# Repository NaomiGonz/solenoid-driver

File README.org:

** Single Channel Solenoid Driver

#+attr_org: :width 500px
[[file:./images/driver-v0.png]]

A prototype single channel solenoid driver was developed for testing.

It is contained in the ~driver-v0~ folder.

We will have 3 manifolds with 8 of these in a row that need to be driven with 12V and signalled with a TTL line. All the manifolds will act in unison.

 - https://www.theleeco.com/product/lhd-series-2-way-control-solenoid-valve/
 - 3 boards, 8 channels each
 - 8 TTL inputs + GND
 - 8 12V outputs
 - 12V input on barrel jack
   - Plug:
     - https://www.digikey.com/en/products/detail/globtek-inc/CRP11856F00/16515770
     - Cable Assembly 2.1mm ID, 5.5mm OD Jack, Right Angle to Wire Leads Round 6.0' (1.83m)
   - Jack:
     - https://www.digikey.com/en/products/detail/cui-devices/PJ-063AH/2161208
     - PJ-063AH Power Barrel Connector Jack 2.10mm ID (0.083"), 5.50mm OD (0.217") Through Hole, Right Angle
 - LHDB1242115H
 - Spike+hold voltage: 12, 7.2
 - LOHM RATE** (Cv): 1500 Lohms (0.013)
 - Power Consumption At Hold Voltage (mW): 310
 - Response time: 10 ms Max

|----+-----------+-----+----------------------+--------------------+---------------------------|
|  # | Reference | Qty | Value                | PartNum            | Mfg                       |
|----+-----------+-----+----------------------+--------------------+---------------------------|
|  1 | C1        |   1 | 47uF                 | T491X476K035AT     | Kemet                     |
|  2 | C3        |   1 | 10uF                 | CL32A106KLULNNE    | Samsung Electro-Mechanics |
|  3 | C4        |   1 | 0.18 uF              | 08053C184KAT2A     | KYOCERA AVX               |
|  4 | C5        |   1 | 470pF                | C0805C471K5RAC7800 | Kemet                     |
|  5 | D1        |   1 | LED                  | 150080RS75000      | Wurth                     |
|  6 | D2        |   1 | PMEG10010ELRX        | PMEG10010ELRX      | Nexperia                  |
|  7 | F1        |   1 | 0ZCF0125FF2C         | 0ZCF0125FF2C       | Bel Fuse                  |
|  8 | J1, J2    |   2 | Screw_Terminal_01x02 | 282837-2           | TE                        |
|  9 | J3        |   1 | Barrel_Jack          | PJ-063AH           | CUI                       |
| 10 | R1        |   1 | 49R9                 | RC0805FR-0749R9L   | Yageo                     |
| 11 | R2        |   1 | 191k                 | RC0805FR-07191KL   | Yageo                     |
| 12 | R3        |   1 | 162k                 | RC0805FR-07162KL   | Yageo                     |
| 13 | R4, R5    |   2 | 4k7                  | RC0805JR-074K7L    | Yageo                     |
| 14 | U1        |   1 | DRV104PWP            | DRV104PWP          | TI                        |
|----+-----------+-----+----------------------+--------------------+---------------------------|

** Octal Channel Driver

** Dual Channel Complementary Driver

We will also have a pair of these valves that need to be driven by a single TTL
line in opposition (if one is in state A the other should be in state B).
 - LHDA1231415H
 - https://www.theleeco.com/product/lhd-series-3-way-control-solenoid-valve/
 - One TTL input  + GND
 - Two 12V complementary outputs

The solenoids should be driven with a high-side switch using a peak and hold circuit.

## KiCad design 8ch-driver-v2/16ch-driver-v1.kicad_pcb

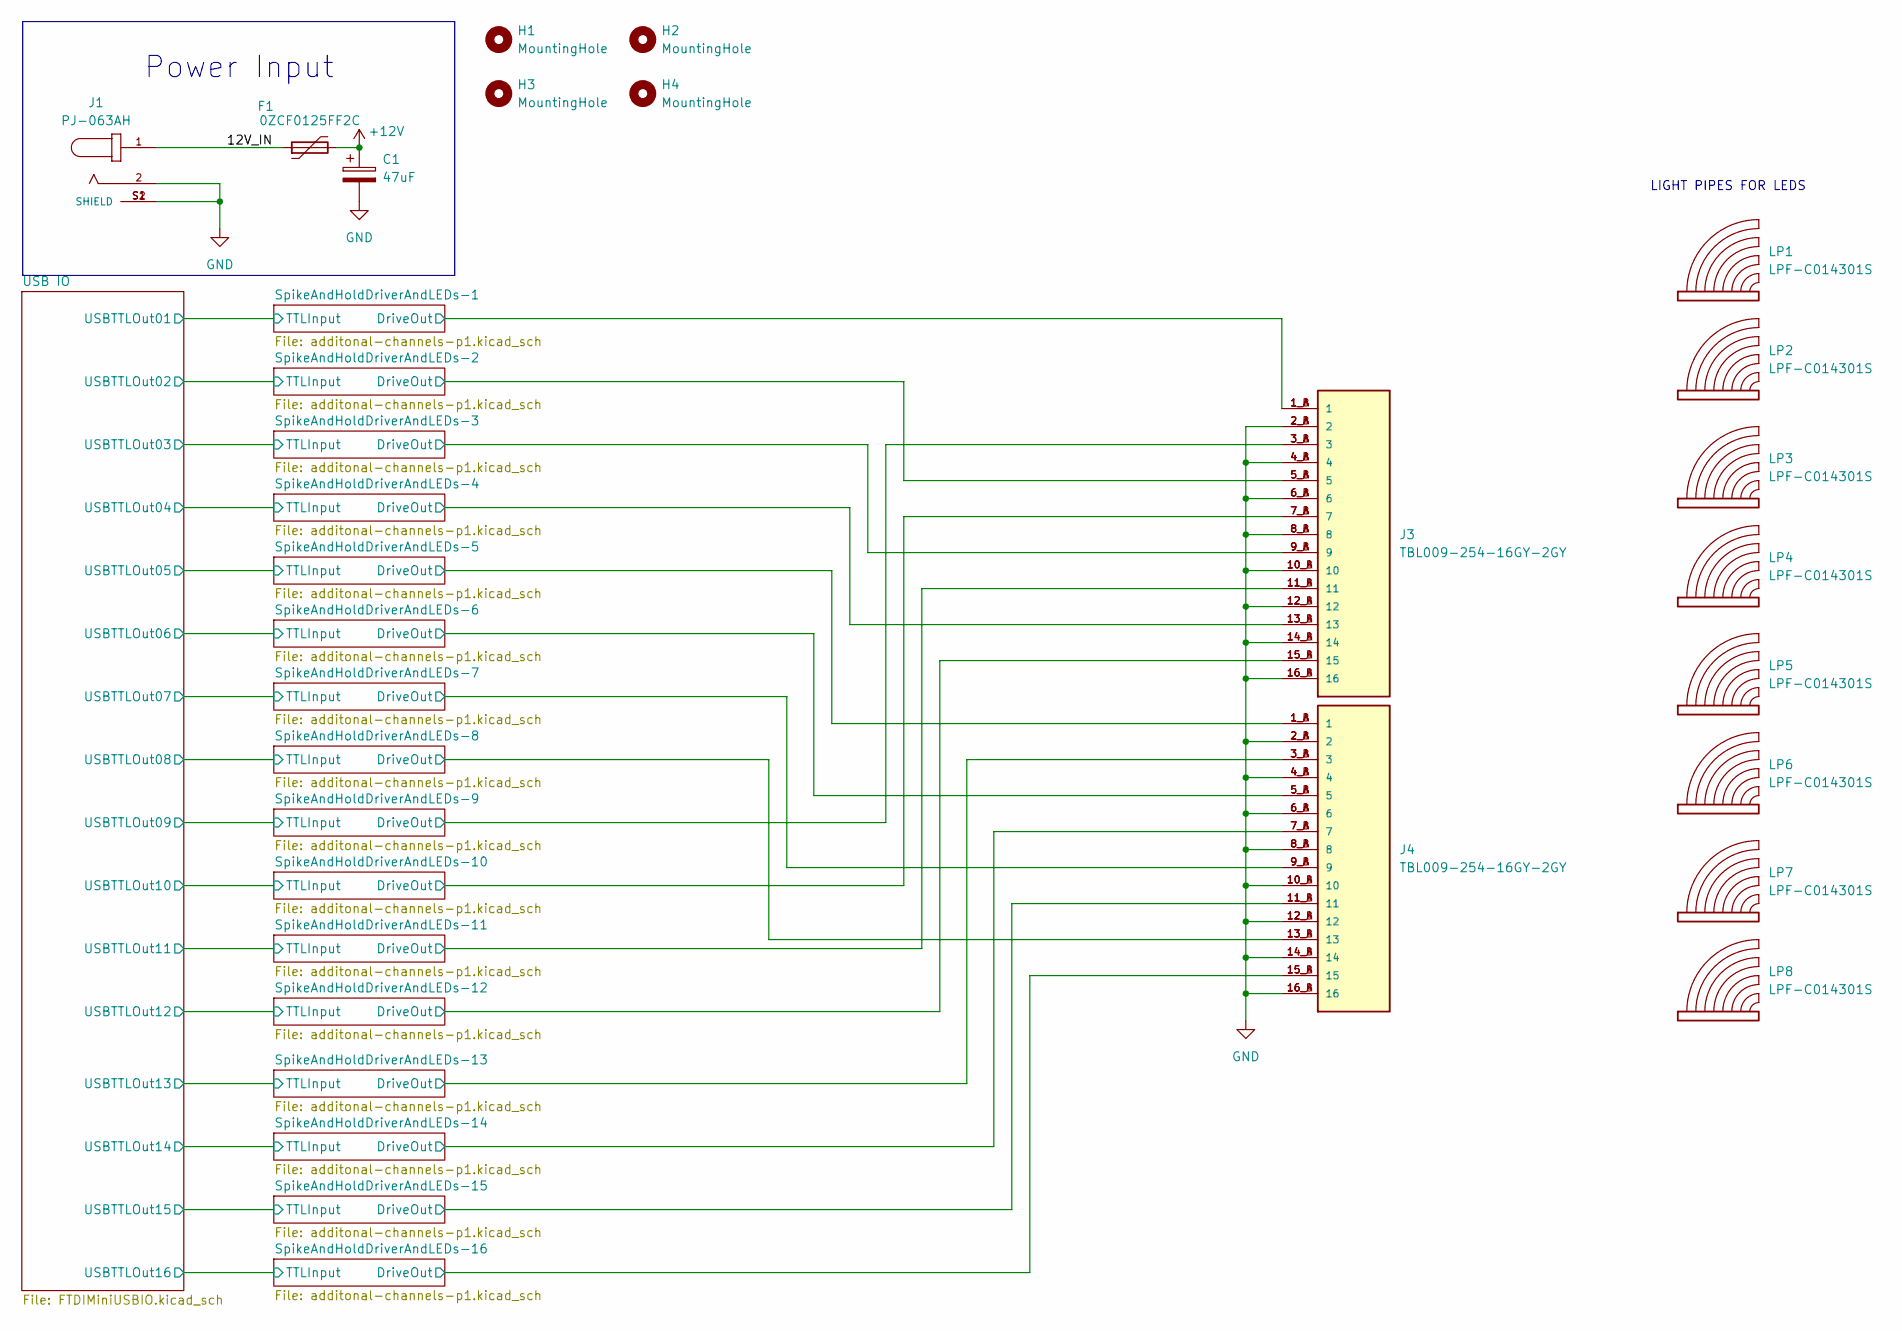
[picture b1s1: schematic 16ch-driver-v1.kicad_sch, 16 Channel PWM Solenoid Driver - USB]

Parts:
C1: 47uF; CP_EIA-7343-43_Kemet-X_Pad2.25x2.55mm_HandSolder; PartNum T491X476K035AT
F1: 0ZCF0125FF2C; Fuse_2920_7451Metric; PartNum 0ZCF0125FF2C
H1, H2, H3, H4: MountingHole; MountingHole_3.2mm_M3
J1: PJ-063AH; CUI_PJ-063AH; PARTREV 1.02
J3, J4: TBL009-254-16GY-2GY; CUI_TBL009-254-16GY-2GY
LP1, LP2, LP3, LP4, LP5, LP6, LP7, LP8: LPF-C014301S; Lightpipe_LPF-C014301S

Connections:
+12V: C1.1, F1.2; also elsewhere on the board
/12V_IN: F1.1, J1.1
/SpikeAndHoldDriverAndLEDs-1/DriveOut: J3.1_A (1), J3.1_B (1); also elsewhere on the board
/SpikeAndHoldDriverAndLEDs-2/DriveOut: J3.5_A (5), J3.5_B (5); also elsewhere on the board
/SpikeAndHoldDriverAndLEDs-3/DriveOut: J3.9_A (9), J3.9_B (9); also elsewhere on the board
/SpikeAndHoldDriverAndLEDs-4/DriveOut: J3.13_A (13), J3.13_B (13); also elsewhere on the board
/SpikeAndHoldDriverAndLEDs-5/DriveOut: J4.1_A (1), J4.1_B (1); also elsewhere on the board
/SpikeAndHoldDriverAndLEDs-6/DriveOut: J4.5_A (5), J4.5_B (5); also elsewhere on the board
/SpikeAndHoldDriverAndLEDs-7/DriveOut: J4.9_A (9), J4.9_B (9); also elsewhere on the board
/SpikeAndHoldDriverAndLEDs-8/DriveOut: J4.13_A (13), J4.13_B (13); also elsewhere on the board
/SpikeAndHoldDriverAndLEDs-9/DriveOut: J3.3_A (3), J3.3_B (3); also elsewhere on the board
/SpikeAndHoldDriverAndLEDs-10/DriveOut: J3.7_A (7), J3.7_B (7); also elsewhere on the board
/SpikeAndHoldDriverAndLEDs-11/DriveOut: J3.11_A (11), J3.11_B (11); also elsewhere on the board
/SpikeAndHoldDriverAndLEDs-12/DriveOut: J3.15_A (15), J3.15_B (15); also elsewhere on the board
/SpikeAndHoldDriverAndLEDs-13/DriveOut: J4.3_A (3), J4.3_B (3); also elsewhere on the board
/SpikeAndHoldDriverAndLEDs-14/DriveOut: J4.7_A (7), J4.7_B (7); also elsewhere on the board
/SpikeAndHoldDriverAndLEDs-15/DriveOut: J4.11_A (11), J4.11_B (11); also elsewhere on the board
/SpikeAndHoldDriverAndLEDs-16/DriveOut: J4.15_A (15), J4.15_B (15); also elsewhere on the board
GND: C1.2, J1.2, J1.S1 (SHIELD), J1.S2 (SHIELD), J3.2_A (2), J3.2_B (2), J3.4_A (4), J3.4_B (4), J3.6_A (6), J3.6_B (6), J3.8_A (8), J3.8_B (8), J3.10_A (10), J3.10_B (10), J3.12_A (12), J3.12_B (12), J3.14_A (14), J3.14_B (14), J3.16_A (16), J3.16_B (16), J4.2_A (2), J4.2_B (2), J4.4_A (4), J4.4_B (4), J4.6_A (6), J4.6_B (6), J4.8_A (8), J4.8_B (8), J4.10_A (10), J4.10_B (10), J4.12_A (12), J4.12_B (12), J4.14_A (14), J4.14_B (14), J4.16_A (16), J4.16_B (16); also elsewhere on the board

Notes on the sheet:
Power Input
LIGHT PIPES FOR LEDS

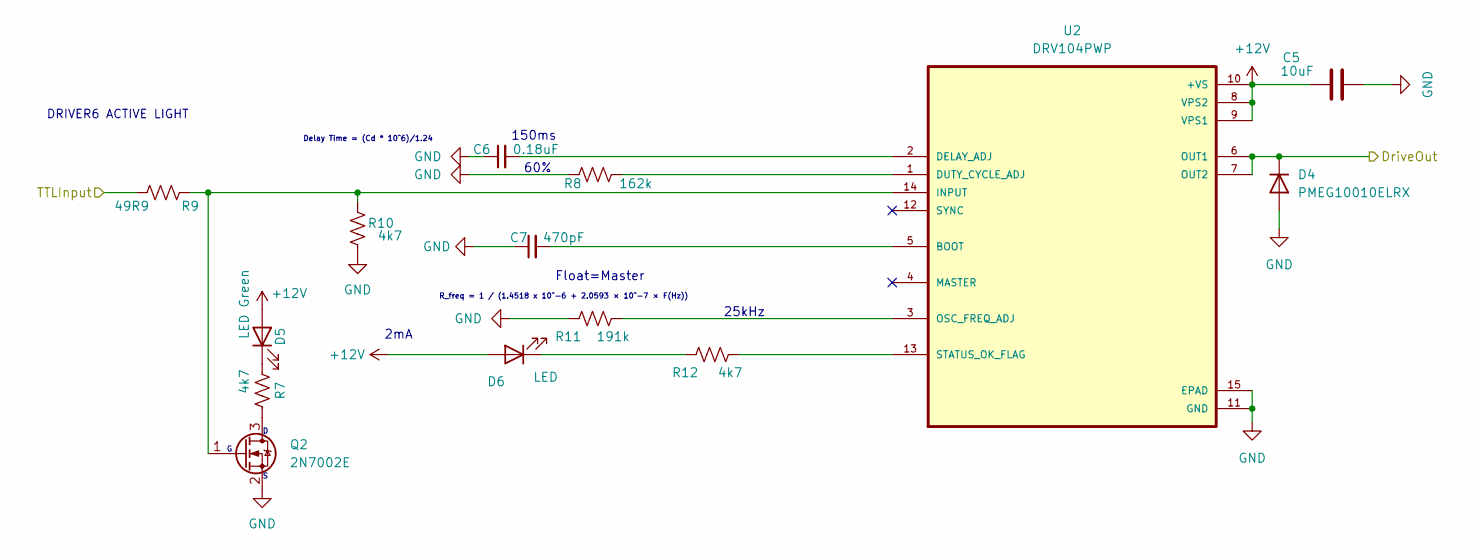
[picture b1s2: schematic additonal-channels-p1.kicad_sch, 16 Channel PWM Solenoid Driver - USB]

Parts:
C5: 10uF; C_1210_3225Metric; PartNum CL32A106KLULNNE
C6: 0.18uF; C_1206_3216Metric; PartNum 08053C184KAT2A
C7: 470pF; C_1206_3216Metric; PartNum C0805C471K5RAC7800
D4: PMEG10010ELRX; Nexperia_CFP3_SOD-123W; PartNum PMEG10010ELRX
D5: LED Green; LED_0805_2012Metric; PartNum 150080RS75000
D6: LED; LED_0805_2012Metric; PartNum 150080RS75000
Q2: 2N7002E; SOT-23
R7: 4k7; R_1206_3216Metric; PartNum RC0805FR-07162KL
R8: 162k; R_1206_3216Metric; PartNum RC0805FR-07162KL
R9: 49R9; R_1206_3216Metric; PartNum RC0805FR-0749R9L
R10, R12: 4k7; R_1206_3216Metric; PartNum RC0805JR-074K7L
R11: 191k; R_1206_3216Metric; PartNum RC0805FR-07191KL
U2: DRV104PWP; IC_TPS27S100BPWPR; PartNum DRV104PWP

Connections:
+12V: C5.1, D5.2 (A), D6.2 (A), U2.8 (VPS2), U2.9 (VPS1), U2.10 (+VS); also elsewhere on the board
/SpikeAndHoldDriverAndLEDs-2/DriveOut: D4.1 (K), U2.6 (OUT1), U2.7 (OUT2); also elsewhere on the board
/SpikeAndHoldDriverAndLEDs-2/TTLInput: R9.1; also elsewhere on the board
GND: C5.2, C6.1, C7.1, D4.2 (A), Q2.2 (S), R8.1, R10.1, R11.1, U2.11 (GND), U2.15 (EPAD); also elsewhere on the board
unnamed: D5.1 (K), R7.1
unnamed: D6.1 (K), R12.1
unnamed: Q2.3 (D), R7.2
unnamed: Q2.1 (G), R9.2, R10.2, U2.14 (INPUT)
unnamed: C7.2, U2.5 (BOOT)
unnamed: C6.2, U2.2 (DELAY_ADJ)
unnamed: R8.2, U2.1 (DUTY_CYCLE_ADJ)
unnamed: R11.2, U2.3 (OSC_FREQ_ADJ)
unnamed: R12.2, U2.13 (STATUS_OK_FLAG)

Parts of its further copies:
C2, C8, C11, C14, C17, C20, C23, C26, C29, C32, C35, C38, C41, C44, C47: 10uF; C_1210_3225Metric; PartNum CL32A106KLULNNE
C3, C9, C12, C15, C18, C21, C24, C27, C30, C33, C36, C39, C42, C45, C48: 0.18uF; C_1206_3216Metric; PartNum 08053C184KAT2A
C4, C10, C13, C16, C19, C22, C25, C28, C31, C34, C37, C40, C43, C46, C49: 470pF; C_1206_3216Metric; PartNum C0805C471K5RAC7800
D1, D7, D10, D13, D16, D19, D22, D25, D28, D31, D34, D37, D40, D43, D46: PMEG10010ELRX; Nexperia_CFP3_SOD-123W; PartNum PMEG10010ELRX
D2, D8, D11, D14, D17, D20, D23, D26, D29, D32, D35, D38, D41, D44, D47: LED Green; LED_0805_2012Metric; PartNum 150080RS75000
D3, D9, D12, D15, D18, D21, D24, D27, D30, D33, D36, D39, D42, D45, D48: LED; LED_0805_2012Metric; PartNum 150080RS75000
Q1, Q3, Q4, Q5, Q6, Q7, Q8, Q9, Q10, Q11, Q12, Q13, Q14, Q15, Q16: 2N7002E; SOT-23
R1, R13, R19, R25, R31, R37, R43, R49, R55, R61, R67, R73, R79, R85, R91: 4k7; R_1206_3216Metric; PartNum RC0805FR-07162KL
R2, R14, R20, R26, R32, R38, R44, R50, R56, R62, R68, R74, R80, R86, R92: 162k; R_1206_3216Metric; PartNum RC0805FR-07162KL
R3, R15, R21, R27, R33, R39, R45, R51, R57, R63, R69, R75, R81, R87, R93: 49R9; R_1206_3216Metric; PartNum RC0805FR-0749R9L
R4, R6, R16, R18, R22, R24, R28, R30, R34, R36, R40, R42, R46, R48, R52, R54, R58, R60, R64, R66, R70, R72, R76, R78, R82, R84, R88, R90, R94, R96: 4k7; R_1206_3216Metric; PartNum RC0805JR-074K7L
R5, R17, R23, R29, R35, R41, R47, R53, R59, R65, R71, R77, R83, R89, R95: 191k; R_1206_3216Metric; PartNum RC0805FR-07191KL
U1, U3, U4, U5, U6, U7, U8, U9, U10, U11, U12, U13, U14, U15, U16: DRV104PWP; IC_TPS27S100BPWPR; PartNum DRV104PWP

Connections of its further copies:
+12V: C2.1, C8.1, C11.1, C14.1, C17.1, C20.1, C23.1, C26.1, C29.1, C32.1, C35.1, C38.1, C41.1, C44.1, C47.1, D2.2 (A), D3.2 (A), D8.2 (A), D9.2 (A), D11.2 (A), D12.2 (A), D14.2 (A), D15.2 (A), D17.2 (A), D18.2 (A), D20.2 (A), D21.2 (A), D23.2 (A), D24.2 (A), D26.2 (A), D27.2 (A), D29.2 (A), D30.2 (A), D32.2 (A), D33.2 (A), D35.2 (A), D36.2 (A), D38.2 (A), D39.2 (A), D41.2 (A), D42.2 (A), D44.2 (A), D45.2 (A), D47.2 (A), D48.2 (A), U1.8 (VPS2), U1.9 (VPS1), U1.10 (+VS), U3.8 (VPS2), U3.9 (VPS1), U3.10 (+VS), U4.8 (VPS2), U4.9 (VPS1), U4.10 (+VS), U5.8 (VPS2), U5.9 (VPS1), U5.10 (+VS), U6.8 (VPS2), U6.9 (VPS1), U6.10 (+VS), U7.8 (VPS2), U7.9 (VPS1), U7.10 (+VS), U8.8 (VPS2), U8.9 (VPS1), U8.10 (+VS), U9.8 (VPS2), U9.9 (VPS1), U9.10 (+VS), U10.8 (VPS2), U10.9 (VPS1), U10.10 (+VS), U11.8 (VPS2), U11.9 (VPS1), U11.10 (+VS), U12.8 (VPS2), U12.9 (VPS1), U12.10 (+VS), U13.8 (VPS2), U13.9 (VPS1), U13.10 (+VS), U14.8 (VPS2), U14.9 (VPS1), U14.10 (+VS), U15.8 (VPS2), U15.9 (VPS1), U15.10 (+VS), U16.8 (VPS2), U16.9 (VPS1), U16.10 (+VS); also elsewhere on the board
/SpikeAndHoldDriverAndLEDs-1/DriveOut: D1.1 (K), U1.6 (OUT1), U1.7 (OUT2); also elsewhere on the board
/SpikeAndHoldDriverAndLEDs-1/TTLInput: R3.1; also elsewhere on the board
/SpikeAndHoldDriverAndLEDs-3/DriveOut: D7.1 (K), U3.6 (OUT1), U3.7 (OUT2); also elsewhere on the board
/SpikeAndHoldDriverAndLEDs-3/TTLInput: R15.1; also elsewhere on the board
/SpikeAndHoldDriverAndLEDs-4/DriveOut: D10.1 (K), U4.6 (OUT1), U4.7 (OUT2); also elsewhere on the board
/SpikeAndHoldDriverAndLEDs-4/TTLInput: R21.1; also elsewhere on the board
/SpikeAndHoldDriverAndLEDs-5/DriveOut: D13.1 (K), U5.6 (OUT1), U5.7 (OUT2); also elsewhere on the board
/SpikeAndHoldDriverAndLEDs-5/TTLInput: R27.1; also elsewhere on the board
/SpikeAndHoldDriverAndLEDs-6/DriveOut: D16.1 (K), U6.6 (OUT1), U6.7 (OUT2); also elsewhere on the board
/SpikeAndHoldDriverAndLEDs-6/TTLInput: R33.1; also elsewhere on the board
/SpikeAndHoldDriverAndLEDs-7/DriveOut: D19.1 (K), U7.6 (OUT1), U7.7 (OUT2); also elsewhere on the board
/SpikeAndHoldDriverAndLEDs-7/TTLInput: R39.1; also elsewhere on the board
/SpikeAndHoldDriverAndLEDs-8/DriveOut: D22.1 (K), U8.6 (OUT1), U8.7 (OUT2); also elsewhere on the board
/SpikeAndHoldDriverAndLEDs-8/TTLInput: R45.1; also elsewhere on the board
/SpikeAndHoldDriverAndLEDs-9/DriveOut: D25.1 (K), U9.6 (OUT1), U9.7 (OUT2); also elsewhere on the board
/SpikeAndHoldDriverAndLEDs-9/TTLInput: R51.1; also elsewhere on the board
/SpikeAndHoldDriverAndLEDs-10/DriveOut: D28.1 (K), U10.6 (OUT1), U10.7 (OUT2); also elsewhere on the board
/SpikeAndHoldDriverAndLEDs-10/TTLInput: R57.1; also elsewhere on the board
/SpikeAndHoldDriverAndLEDs-11/DriveOut: D31.1 (K), U11.6 (OUT1), U11.7 (OUT2); also elsewhere on the board
/SpikeAndHoldDriverAndLEDs-11/TTLInput: R63.1; also elsewhere on the board
/SpikeAndHoldDriverAndLEDs-12/DriveOut: D34.1 (K), U12.6 (OUT1), U12.7 (OUT2); also elsewhere on the board
/SpikeAndHoldDriverAndLEDs-12/TTLInput: R69.1; also elsewhere on the board
/SpikeAndHoldDriverAndLEDs-13/DriveOut: D37.1 (K), U13.6 (OUT1), U13.7 (OUT2); also elsewhere on the board
/SpikeAndHoldDriverAndLEDs-13/TTLInput: R75.1; also elsewhere on the board
/SpikeAndHoldDriverAndLEDs-14/DriveOut: D40.1 (K), U14.6 (OUT1), U14.7 (OUT2); also elsewhere on the board
/SpikeAndHoldDriverAndLEDs-14/TTLInput: R81.1; also elsewhere on the board
/SpikeAndHoldDriverAndLEDs-15/DriveOut: D43.1 (K), U15.6 (OUT1), U15.7 (OUT2); also elsewhere on the board
/SpikeAndHoldDriverAndLEDs-15/TTLInput: R87.1; also elsewhere on the board
/SpikeAndHoldDriverAndLEDs-16/DriveOut: D46.1 (K), U16.6 (OUT1), U16.7 (OUT2); also elsewhere on the board
/SpikeAndHoldDriverAndLEDs-16/TTLInput: R93.1; also elsewhere on the board
GND: C2.2, C3.1, C4.1, C8.2, C9.1, C10.1, C11.2, C12.1, C13.1, C14.2, C15.1, C16.1, C17.2, C18.1, C19.1, C20.2, C21.1, C22.1, C23.2, C24.1, C25.1, C26.2, C27.1, C28.1, C29.2, C30.1, C31.1, C32.2, C33.1, C34.1, C35.2, C36.1, C37.1, C38.2, C39.1, C40.1, C41.2, C42.1, C43.1, C44.2, C45.1, C46.1, C47.2, C48.1, C49.1, D1.2 (A), D7.2 (A), D10.2 (A), D13.2 (A), D16.2 (A), D19.2 (A), D22.2 (A), D25.2 (A), D28.2 (A), D31.2 (A), D34.2 (A), D37.2 (A), D40.2 (A), D43.2 (A), D46.2 (A), Q1.2 (S), Q3.2 (S), Q4.2 (S), Q5.2 (S), Q6.2 (S), Q7.2 (S), Q8.2 (S), Q9.2 (S), Q10.2 (S), Q11.2 (S), Q12.2 (S), Q13.2 (S), Q14.2 (S), Q15.2 (S), Q16.2 (S), R2.1, R4.1, R5.1, R14.1, R16.1, R17.1, R20.1, R22.1, R23.1, R26.1, R28.1, R29.1, R32.1, R34.1, R35.1, R38.1, R40.1, R41.1, R44.1, R46.1, R47.1, R50.1, R52.1, R53.1, R56.1, R58.1, R59.1, R62.1, R64.1, R65.1, R68.1, R70.1, R71.1, R74.1, R76.1, R77.1, R80.1, R82.1, R83.1, R86.1, R88.1, R89.1, R92.1, R94.1, R95.1, U1.11 (GND), U1.15 (EPAD), U3.11 (GND), U3.15 (EPAD), U4.11 (GND), U4.15 (EPAD), U5.11 (GND), U5.15 (EPAD), U6.11 (GND), U6.15 (EPAD), U7.11 (GND), U7.15 (EPAD), U8.11 (GND), U8.15 (EPAD), U9.11 (GND), U9.15 (EPAD), U10.11 (GND), U10.15 (EPAD), U11.11 (GND), U11.15 (EPAD), U12.11 (GND), U12.15 (EPAD), U13.11 (GND), U13.15 (EPAD), U14.11 (GND), U14.15 (EPAD), U15.11 (GND), U15.15 (EPAD), U16.11 (GND), U16.15 (EPAD); also elsewhere on the board
unnamed: D2.1 (K), R1.1
unnamed: D3.1 (K), R6.1
unnamed: D8.1 (K), R13.1
unnamed: D9.1 (K), R18.1
unnamed: D11.1 (K), R19.1
unnamed: D12.1 (K), R24.1
unnamed: D14.1 (K), R25.1
unnamed: D15.1 (K), R30.1
unnamed: D17.1 (K), R31.1
unnamed: D18.1 (K), R36.1
unnamed: D20.1 (K), R37.1
unnamed: D21.1 (K), R42.1
unnamed: D23.1 (K), R43.1
unnamed: D24.1 (K), R48.1
unnamed: D26.1 (K), R49.1
unnamed: D27.1 (K), R54.1
unnamed: D29.1 (K), R55.1
unnamed: D30.1 (K), R60.1
unnamed: D32.1 (K), R61.1
unnamed: D33.1 (K), R66.1
unnamed: D35.1 (K), R67.1
unnamed: D36.1 (K), R72.1
unnamed: D38.1 (K), R73.1
unnamed: D39.1 (K), R78.1
unnamed: D41.1 (K), R79.1
unnamed: D42.1 (K), R84.1
unnamed: D44.1 (K), R85.1
unnamed: D45.1 (K), R90.1
unnamed: D47.1 (K), R91.1
unnamed: D48.1 (K), R96.1
unnamed: Q1.3 (D), R1.2
unnamed: Q1.1 (G), R3.2, R4.2, U1.14 (INPUT)
unnamed: Q3.3 (D), R13.2
unnamed: Q3.1 (G), R15.2, R16.2, U3.14 (INPUT)
unnamed: Q4.3 (D), R19.2
unnamed: Q4.1 (G), R21.2, R22.2, U4.14 (INPUT)
unnamed: Q5.3 (D), R25.2
unnamed: Q5.1 (G), R27.2, R28.2, U5.14 (INPUT)
unnamed: Q6.3 (D), R31.2
unnamed: Q6.1 (G), R33.2, R34.2, U6.14 (INPUT)
unnamed: Q7.3 (D), R37.2
unnamed: Q7.1 (G), R39.2, R40.2, U7.14 (INPUT)
unnamed: Q8.3 (D), R43.2
unnamed: Q8.1 (G), R45.2, R46.2, U8.14 (INPUT)
unnamed: Q9.3 (D), R49.2
unnamed: Q9.1 (G), R51.2, R52.2, U9.14 (INPUT)
unnamed: Q10.3 (D), R55.2
unnamed: Q10.1 (G), R57.2, R58.2, U10.14 (INPUT)
unnamed: Q11.3 (D), R61.2
unnamed: Q11.1 (G), R63.2, R64.2, U11.14 (INPUT)
unnamed: Q12.3 (D), R67.2
unnamed: Q12.1 (G), R69.2, R70.2, U12.14 (INPUT)
unnamed: Q13.3 (D), R73.2
unnamed: Q13.1 (G), R75.2, R76.2, U13.14 (INPUT)
unnamed: Q14.3 (D), R79.2
unnamed: Q14.1 (G), R81.2, R82.2, U14.14 (INPUT)
unnamed: Q15.3 (D), R85.2
unnamed: Q15.1 (G), R87.2, R88.2, U15.14 (INPUT)
unnamed: Q16.3 (D), R91.2
unnamed: Q16.1 (G), R93.2, R94.2, U16.14 (INPUT)
unnamed: C4.2, U1.5 (BOOT)
unnamed: C3.2, U1.2 (DELAY_ADJ)
unnamed: R2.2, U1.1 (DUTY_CYCLE_ADJ)
unnamed: R5.2, U1.3 (OSC_FREQ_ADJ)
unnamed: R6.2, U1.13 (STATUS_OK_FLAG)
unnamed: C10.2, U3.5 (BOOT)
unnamed: C9.2, U3.2 (DELAY_ADJ)
unnamed: R14.2, U3.1 (DUTY_CYCLE_ADJ)
unnamed: R17.2, U3.3 (OSC_FREQ_ADJ)
unnamed: R18.2, U3.13 (STATUS_OK_FLAG)
unnamed: C13.2, U4.5 (BOOT)
unnamed: C12.2, U4.2 (DELAY_ADJ)
unnamed: R20.2, U4.1 (DUTY_CYCLE_ADJ)
unnamed: R23.2, U4.3 (OSC_FREQ_ADJ)
unnamed: R24.2, U4.13 (STATUS_OK_FLAG)
unnamed: C16.2, U5.5 (BOOT)
unnamed: C15.2, U5.2 (DELAY_ADJ)
unnamed: R26.2, U5.1 (DUTY_CYCLE_ADJ)
unnamed: R29.2, U5.3 (OSC_FREQ_ADJ)
unnamed: R30.2, U5.13 (STATUS_OK_FLAG)
unnamed: C19.2, U6.5 (BOOT)
unnamed: C18.2, U6.2 (DELAY_ADJ)
unnamed: R32.2, U6.1 (DUTY_CYCLE_ADJ)
unnamed: R35.2, U6.3 (OSC_FREQ_ADJ)
unnamed: R36.2, U6.13 (STATUS_OK_FLAG)
unnamed: C22.2, U7.5 (BOOT)
unnamed: C21.2, U7.2 (DELAY_ADJ)
unnamed: R38.2, U7.1 (DUTY_CYCLE_ADJ)
unnamed: R41.2, U7.3 (OSC_FREQ_ADJ)
unnamed: R42.2, U7.13 (STATUS_OK_FLAG)
unnamed: C25.2, U8.5 (BOOT)
unnamed: C24.2, U8.2 (DELAY_ADJ)
unnamed: R44.2, U8.1 (DUTY_CYCLE_ADJ)
unnamed: R47.2, U8.3 (OSC_FREQ_ADJ)
unnamed: R48.2, U8.13 (STATUS_OK_FLAG)
unnamed: C28.2, U9.5 (BOOT)
unnamed: C27.2, U9.2 (DELAY_ADJ)
unnamed: R50.2, U9.1 (DUTY_CYCLE_ADJ)
unnamed: R53.2, U9.3 (OSC_FREQ_ADJ)
unnamed: R54.2, U9.13 (STATUS_OK_FLAG)
unnamed: C31.2, U10.5 (BOOT)
unnamed: C30.2, U10.2 (DELAY_ADJ)
unnamed: R56.2, U10.1 (DUTY_CYCLE_ADJ)
unnamed: R59.2, U10.3 (OSC_FREQ_ADJ)
unnamed: R60.2, U10.13 (STATUS_OK_FLAG)
unnamed: C34.2, U11.5 (BOOT)
unnamed: C33.2, U11.2 (DELAY_ADJ)
unnamed: R62.2, U11.1 (DUTY_CYCLE_ADJ)
unnamed: R65.2, U11.3 (OSC_FREQ_ADJ)
unnamed: R66.2, U11.13 (STATUS_OK_FLAG)
unnamed: C37.2, U12.5 (BOOT)
unnamed: C36.2, U12.2 (DELAY_ADJ)
unnamed: R68.2, U12.1 (DUTY_CYCLE_ADJ)
unnamed: R71.2, U12.3 (OSC_FREQ_ADJ)
unnamed: R72.2, U12.13 (STATUS_OK_FLAG)
unnamed: C40.2, U13.5 (BOOT)
unnamed: C39.2, U13.2 (DELAY_ADJ)
unnamed: R74.2, U13.1 (DUTY_CYCLE_ADJ)
unnamed: R77.2, U13.3 (OSC_FREQ_ADJ)
unnamed: R78.2, U13.13 (STATUS_OK_FLAG)
unnamed: C43.2, U14.5 (BOOT)
unnamed: C42.2, U14.2 (DELAY_ADJ)
unnamed: R80.2, U14.1 (DUTY_CYCLE_ADJ)
unnamed: R83.2, U14.3 (OSC_FREQ_ADJ)
unnamed: R84.2, U14.13 (STATUS_OK_FLAG)
unnamed: C46.2, U15.5 (BOOT)
unnamed: C45.2, U15.2 (DELAY_ADJ)
unnamed: R86.2, U15.1 (DUTY_CYCLE_ADJ)
unnamed: R89.2, U15.3 (OSC_FREQ_ADJ)
unnamed: R90.2, U15.13 (STATUS_OK_FLAG)
unnamed: C49.2, U16.5 (BOOT)
unnamed: C48.2, U16.2 (DELAY_ADJ)
unnamed: R92.2, U16.1 (DUTY_CYCLE_ADJ)
unnamed: R95.2, U16.3 (OSC_FREQ_ADJ)
unnamed: R96.2, U16.13 (STATUS_OK_FLAG)

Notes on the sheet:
2mA
60%
150ms
Float=Master
25kHz
Delay Time = (Cd * 10^6)/1.24
DRIVER6 ACTIVE LIGHT
R_freq = 1 / (1.4518 x 10^−6 + 2.0593 × 10^−7 × F(Hz))

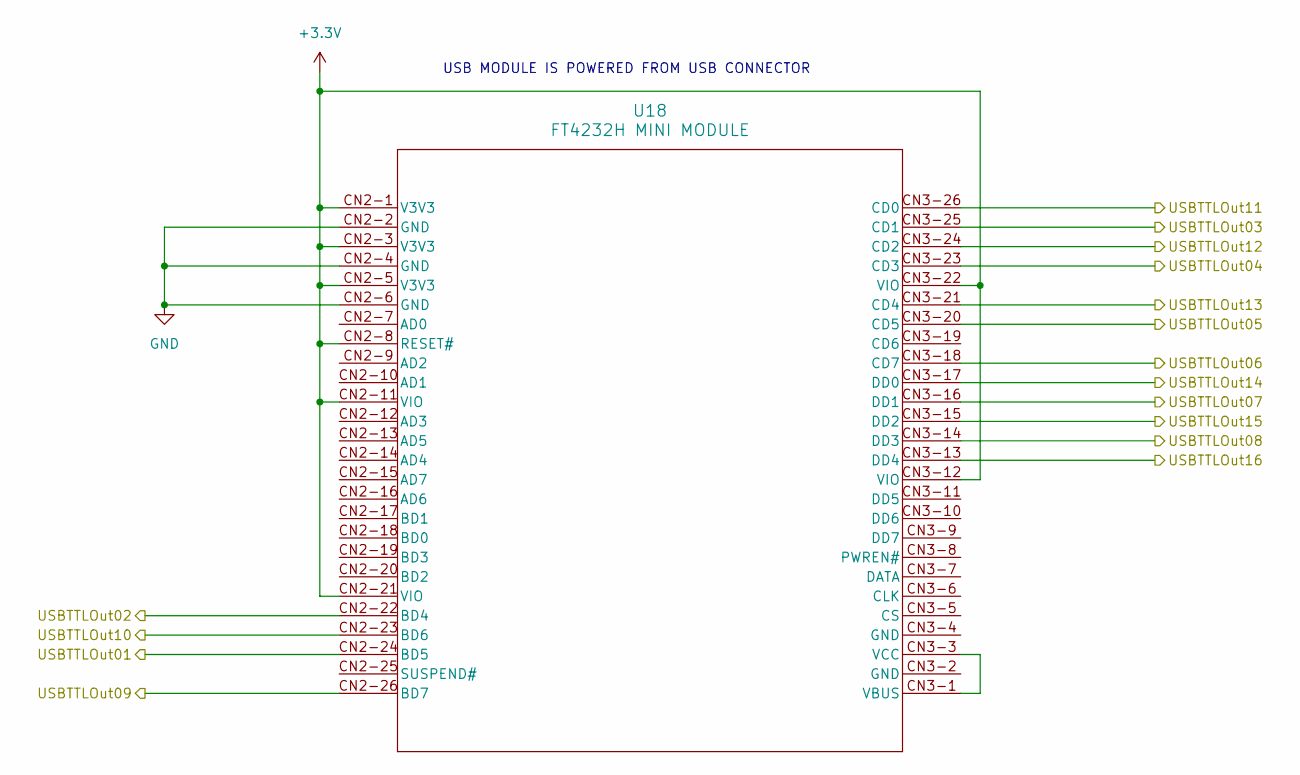
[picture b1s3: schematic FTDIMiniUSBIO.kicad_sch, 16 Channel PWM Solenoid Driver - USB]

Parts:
U18: FT4232H MINI MODULE; FT4232H_MINI_MODULE

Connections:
+3.3V: U18.CN2-1 (V3V3), U18.CN2-3 (V3V3), U18.CN2-5 (V3V3), U18.CN2-8 (RESET#), U18.CN2-11 (VIO), U18.CN2-21 (VIO), U18.CN3-12 (VIO), U18.CN3-22 (VIO)
/SpikeAndHoldDriverAndLEDs-1/TTLInput: U18.CN2-24 (BD5); also elsewhere on the board
/SpikeAndHoldDriverAndLEDs-2/TTLInput: U18.CN2-22 (BD4); also elsewhere on the board
/SpikeAndHoldDriverAndLEDs-3/TTLInput: U18.CN3-25 (CD1); also elsewhere on the board
/SpikeAndHoldDriverAndLEDs-4/TTLInput: U18.CN3-23 (CD3); also elsewhere on the board
/SpikeAndHoldDriverAndLEDs-5/TTLInput: U18.CN3-20 (CD5); also elsewhere on the board
/SpikeAndHoldDriverAndLEDs-6/TTLInput: U18.CN3-18 (CD7); also elsewhere on the board
/SpikeAndHoldDriverAndLEDs-7/TTLInput: U18.CN3-16 (DD1); also elsewhere on the board
/SpikeAndHoldDriverAndLEDs-8/TTLInput: U18.CN3-14 (DD3); also elsewhere on the board
/SpikeAndHoldDriverAndLEDs-9/TTLInput: U18.CN2-26 (BD7); also elsewhere on the board
/SpikeAndHoldDriverAndLEDs-10/TTLInput: U18.CN2-23 (BD6); also elsewhere on the board
/SpikeAndHoldDriverAndLEDs-11/TTLInput: U18.CN3-26 (CD0); also elsewhere on the board
/SpikeAndHoldDriverAndLEDs-12/TTLInput: U18.CN3-24 (CD2); also elsewhere on the board
/SpikeAndHoldDriverAndLEDs-13/TTLInput: U18.CN3-21 (CD4); also elsewhere on the board
/SpikeAndHoldDriverAndLEDs-14/TTLInput: U18.CN3-17 (DD0); also elsewhere on the board
/SpikeAndHoldDriverAndLEDs-15/TTLInput: U18.CN3-15 (DD2); also elsewhere on the board
/SpikeAndHoldDriverAndLEDs-16/TTLInput: U18.CN3-13 (DD4); also elsewhere on the board
GND: U18.CN2-2 (GND), U18.CN2-4 (GND), U18.CN2-6 (GND); also elsewhere on the board
unnamed: U18.CN3-1 (VBUS), U18.CN3-3 (VCC)

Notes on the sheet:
USB MODULE IS POWERED FROM USB CONNECTOR

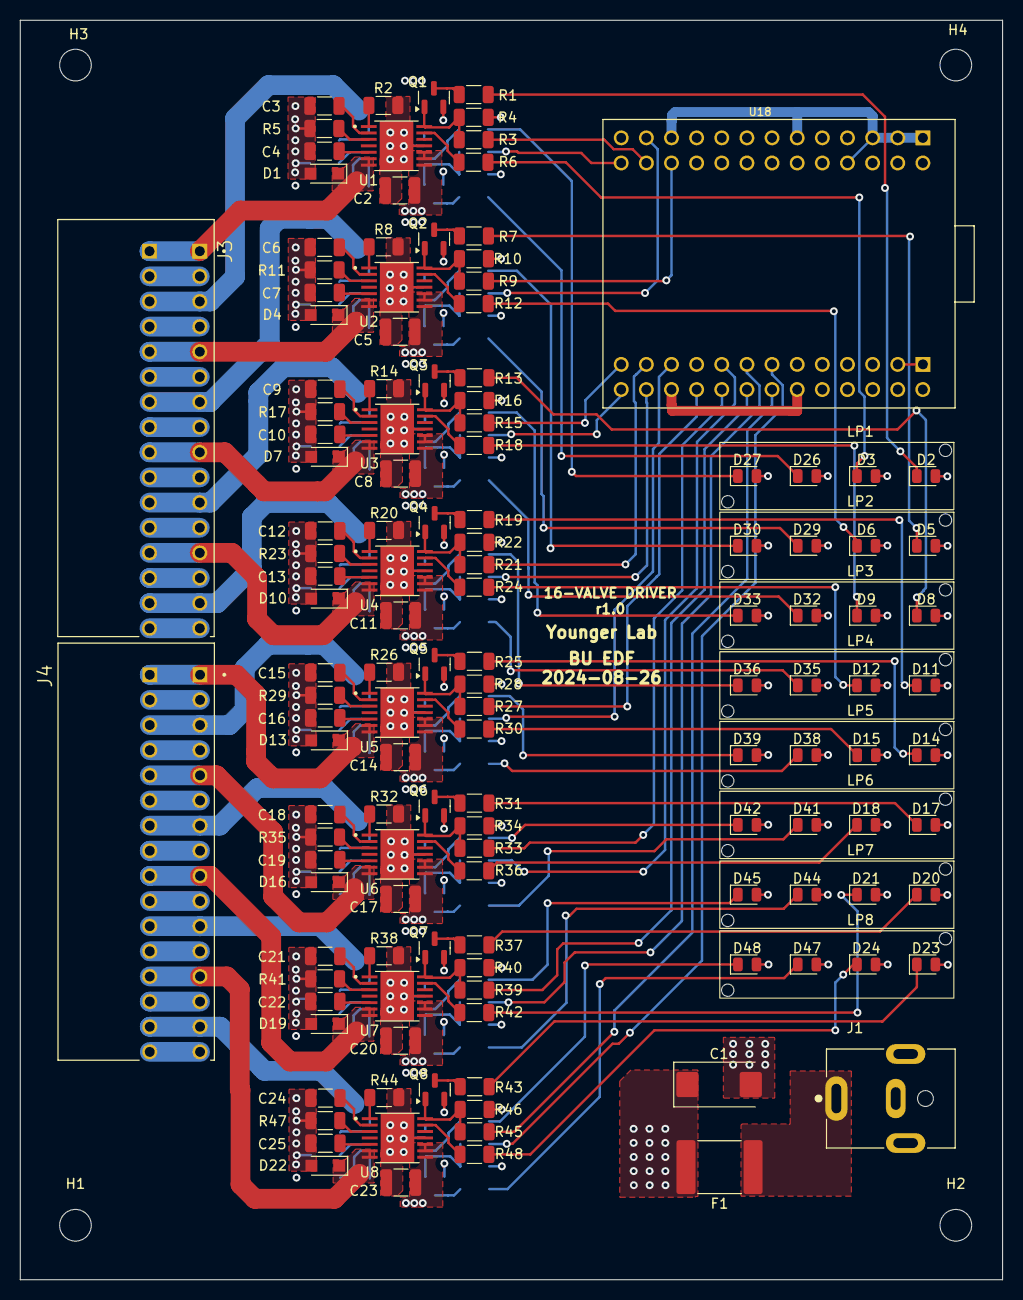
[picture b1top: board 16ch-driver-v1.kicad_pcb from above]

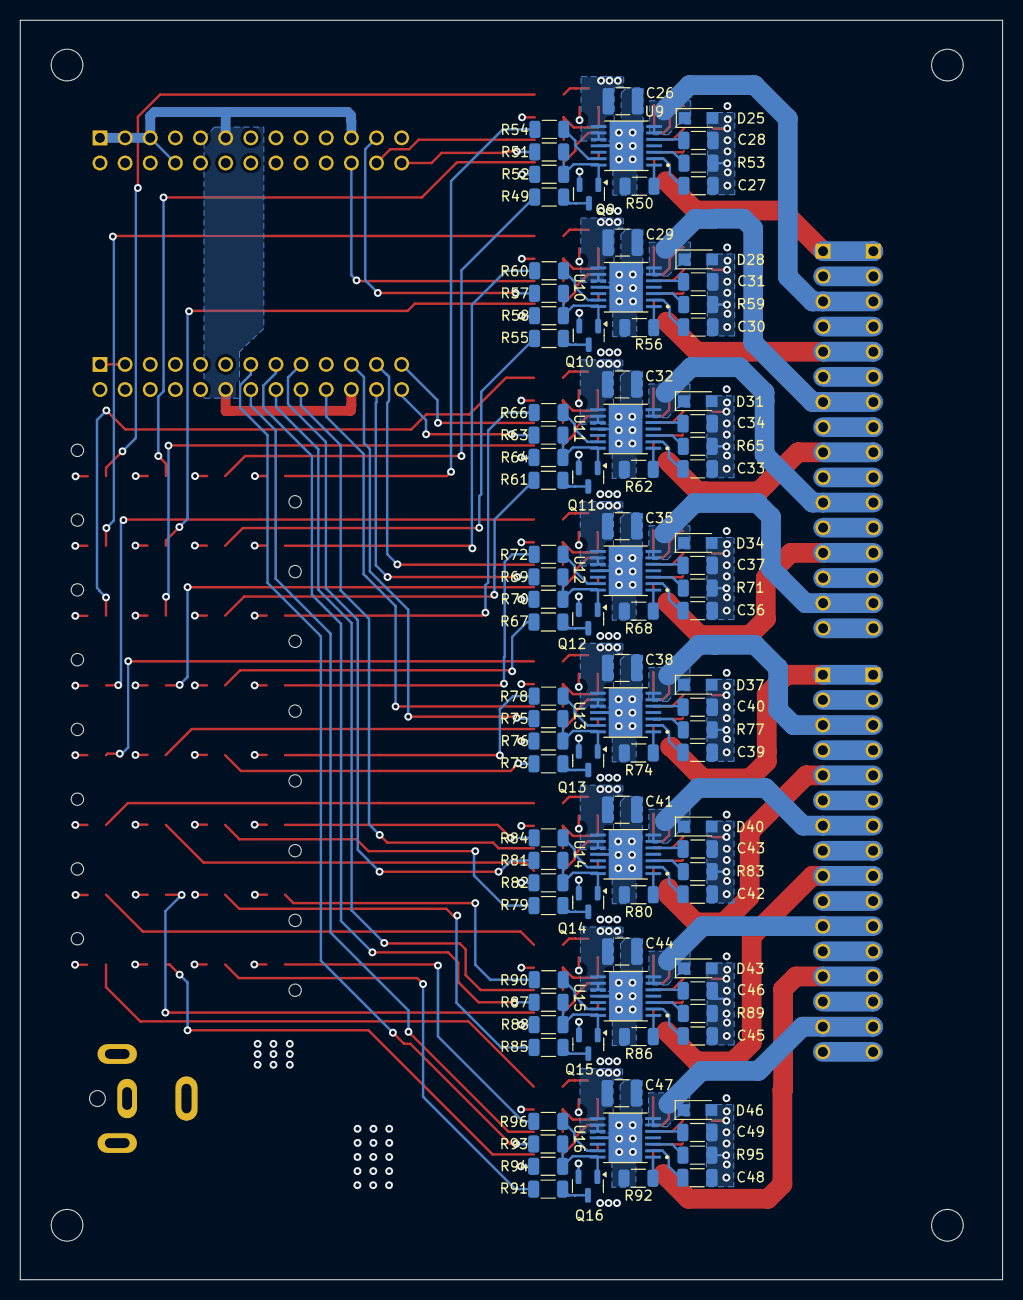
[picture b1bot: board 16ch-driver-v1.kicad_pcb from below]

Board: 4 copper layers, 99.2 x 127.2 mm, 242 parts (96 on the bottom side), 181 nets.
